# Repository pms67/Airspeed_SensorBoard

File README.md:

# Airspeed_SensorBoard
 
Differential pressure sensor breakout board with STM32 (I2C-to-SPI) interface.

Repo contains all necessary files for ordering this board, including assembly, at JLCPCB.com (https://jlcpcb.com/RHS).

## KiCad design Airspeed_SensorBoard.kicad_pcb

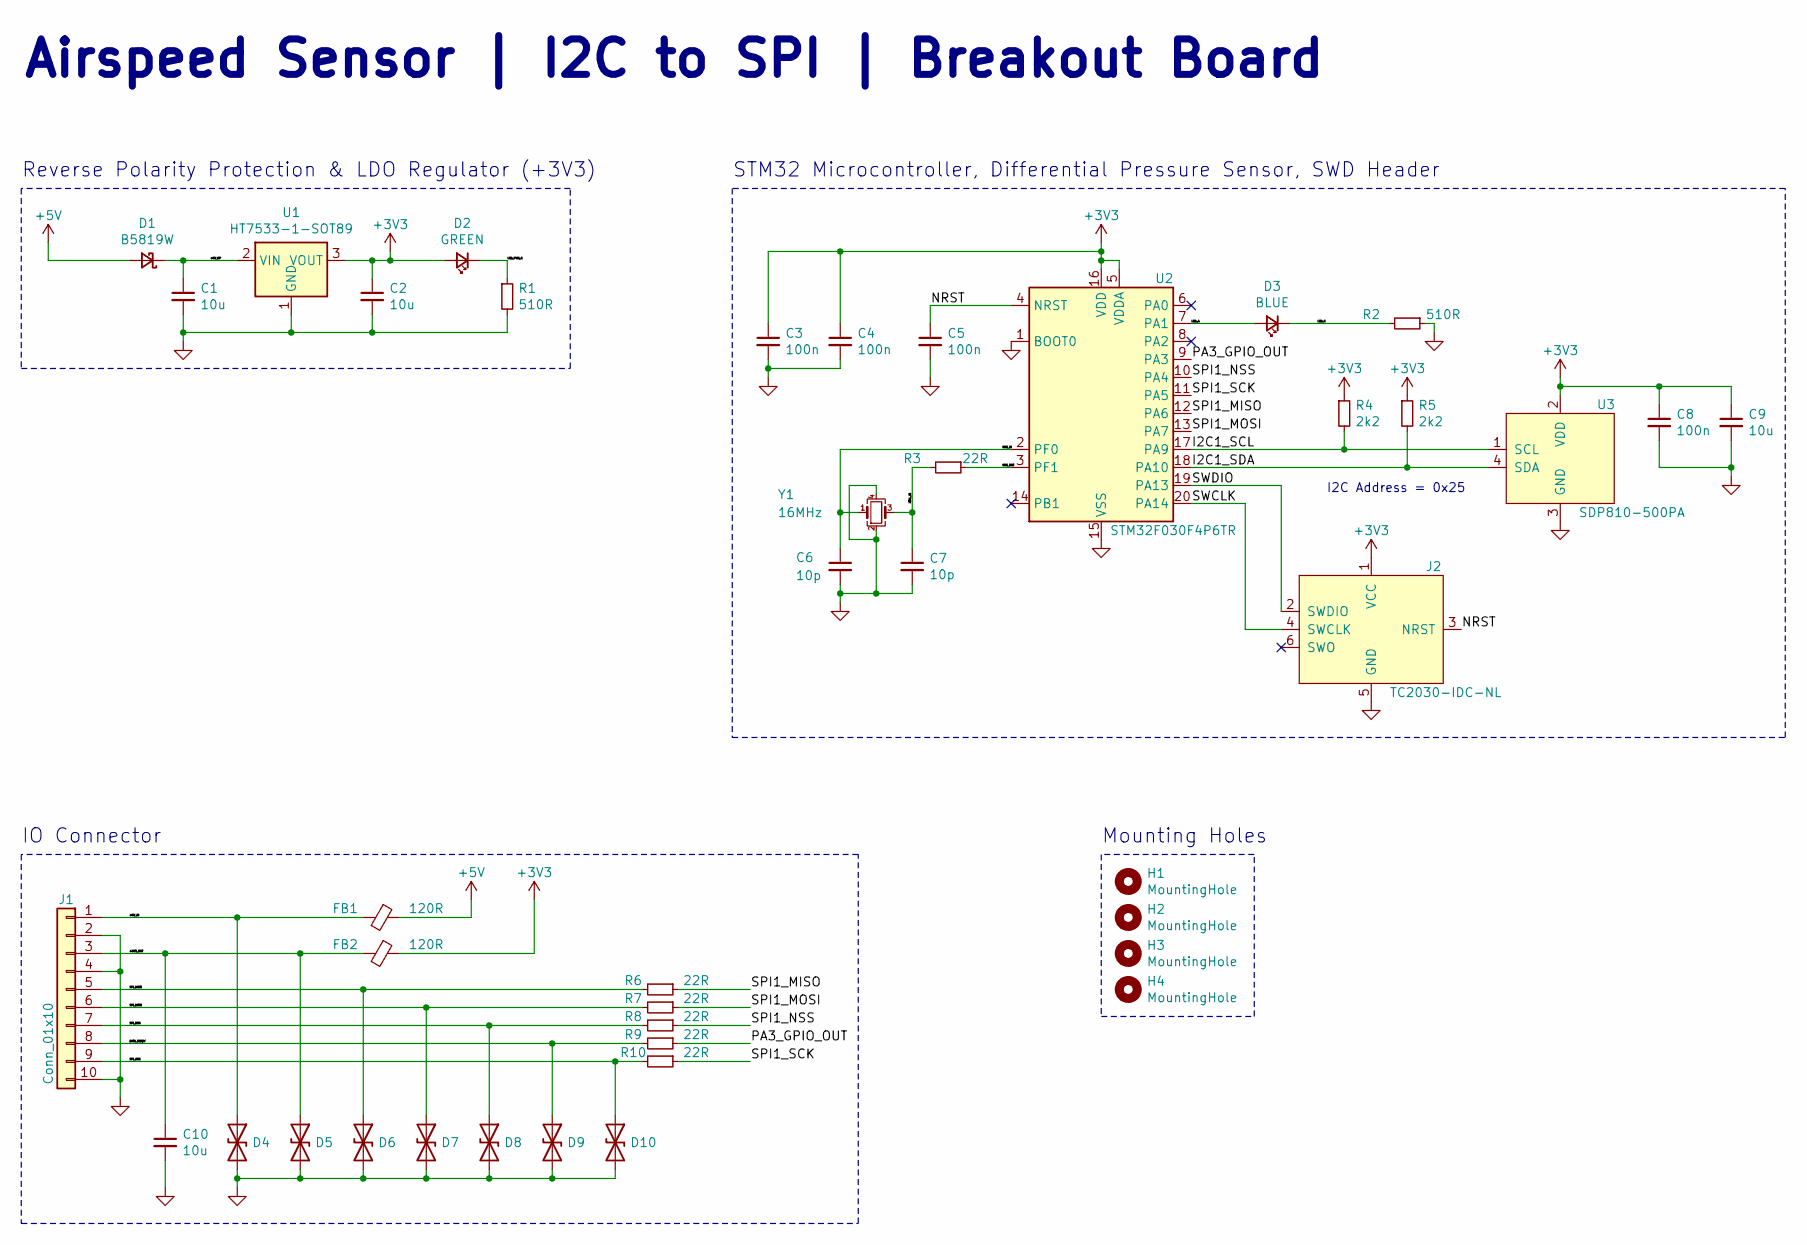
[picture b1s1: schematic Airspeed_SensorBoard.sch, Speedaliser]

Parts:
C1, C2, C9, C10: 10u; C_0805_2012Metric; LCSC Part # C15850
C3, C4, C5, C8: 100n; C_0402_1005Metric; LCSC Part # C1525
C6, C7: 10p; C_0402_1005Metric; LCSC Part # C32949
D1: B5819W; D_SOD-123; LCSC Part # C8598
D2: GREEN; LED_0603_1608Metric; LCSC Part # C72043
D3: BLUE; LED_0603_1608Metric; LCSC Part # C72041
D4, D5, D6, D7, D8, D9, D10: PESD5V0L1BA,115; D_SOD-323; LCSC Part # C85380
FB1, FB2: 120R; L_0603_1608Metric; LCSC Part # C85831
H1, H2, H3, H4: MountingHole; MountingHole_2.2mm_M2
J1: Conn_01x10; Molex_PicoBlade_53048-1010_1x10_P1.25mm_Horizontal
J2: TC2030-IDC-NL
R1, R2: 510R; R_0402_1005Metric; LCSC Part # C25123
R3, R6, R7, R8, R9, R10: 22R; R_0402_1005Metric; LCSC Part # C25092
R4, R5: 2k2; R_0402_1005Metric; LCSC Part # C25879
U1: HT7533-1-SOT89; SOT-89-3; LCSC Part # C14289
U2: STM32F030F4P6TR; TSSOP-20_4.4x6.5mm_P0.65mm; LCSC Part # C89040
U3: SDP810-500PA; LCSC Part # C153056
Y1: 16MHz; Crystal_SMD_3225-4Pin_3.2x2.5mm; LCSC Part # C13738

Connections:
+3V3: C2.1, C3.1, C4.1, C8.1, C9.1, D2.2 (A), FB2.1, J2.1 (VCC), R4.1, R5.1, U1.3 (VOUT), U2.5 (VDDA), U2.16 (VDD), U3.2 (VDD)
+5V: D1.2 (A), FB1.1
/+3V3_OUT: C10.1, D5.1 (A1), FB2.2, J1.3
/+5V_IN: D4.1 (A1), FB1.2, J1.1
/+5V_RP: C1.1, D1.1 (K), U1.2 (VIN)
/DATA_READY: D9.1 (A1), J1.8, R9.2
/HSE_IN: C6.1, U2.2 (PF0), Y1.1
/HSE_OUT: R3.1, U2.3 (PF1)
/I2C1_SCL: R4.2, U2.17 (PA9), U3.1 (SCL)
/I2C1_SDA: R5.2, U2.18 (PA10), U3.4 (SDA)
/LED_A: D3.2 (A), U2.7 (PA1)
/LED_K: D3.1 (K), R2.2
/LED_PWR_K: D2.1 (K), R1.1
/NRST: C5.1, J2.3 (NRST), U2.4 (NRST)
/PA3_GPIO_OUT: R9.1, U2.9 (PA3)
/SPI1_MISO: R6.1, U2.12 (PA6)
/SPI1_MOSI: R7.1, U2.13 (PA7)
/SPI1_NSS: R8.1, U2.10 (PA4)
/SPI1_SCK: R10.1, U2.11 (PA5)
/SPI_MISO: D6.1 (A1), J1.5, R6.2
/SPI_MOSI: D7.1 (A1), J1.6, R7.2
/SPI_NSS: D8.1 (A1), J1.7, R8.2
/SPI_SCK: D10.1 (A1), J1.9, R10.2
/SWCLK: J2.4 (SWCLK), U2.20 (PA14)
/SWDIO: J2.2 (SWDIO), U2.19 (PA13)
/XTAL_IN: C7.1, R3.2, Y1.3
GND: C1.2, C2.2, C3.2, C4.2, C5.2, C6.2, C7.2, C8.2, C9.2, C10.2, D4.2 (A2), D5.2 (A2), D6.2 (A2), D7.2 (A2), D8.2 (A2), D9.2 (A2), D10.2 (A2), J1.2, J1.4, J1.10, J2.5 (GND), R1.2, R2.1, U1.1 (GND), U2.1 (BOOT0), U2.15 (VSS), U3.3 (GND), Y1.2, Y1.4

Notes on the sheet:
I2C Address = 0x25
Reverse Polarity Protection & LDO Regulator (+3V3)
STM32 Microcontroller, Differential Pressure Sensor, SWD Header
Mounting Holes
IO Connector
Airspeed Sensor | I2C to SPI | Breakout Board

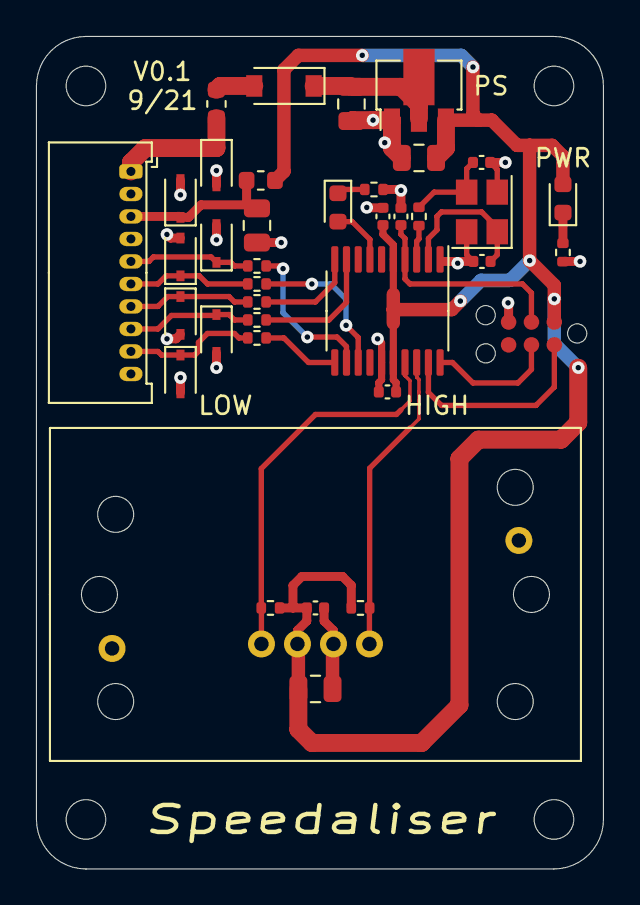
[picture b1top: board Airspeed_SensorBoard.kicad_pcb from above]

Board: 2 copper layers, 31.5 x 46.2 mm, 42 parts (0 on the bottom side), 27 nets.

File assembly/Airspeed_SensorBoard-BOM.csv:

"Designator","Quantity","Value","Cmp name","Footprint","Description","Vendor","LCSC Part #"
"C1, C2, C9, C10, ","4","10u","C_Small","Capacitor_SMD:C_0805_2012Metric","Unpolarized capacitor, small symbol","","C15850"
"C3, C4, C5, C8, ","4","100n","C_Small","Capacitor_SMD:C_0402_1005Metric","Unpolarized capacitor, small symbol","","C1525"
"C6, C7, ","2","10p","C_Small","Capacitor_SMD:C_0402_1005Metric","Unpolarized capacitor, small symbol","","C32949"
"D1, ","1","B5819W","D_Schottky_Small","Diode_SMD:D_SOD-123","Schottky diode, small symbol","","C8598"
"D2, ","1","GREEN","LED_Small","LED_SMD:LED_0603_1608Metric","Light emitting diode, small symbol","","C72043"
"D3, ","1","BLUE","LED_Small","LED_SMD:LED_0603_1608Metric","Light emitting diode, small symbol","","C72041"
"D4, D5, D6, D7, D8, D9, D10, ","7","PESD5V0L1BA,115","D_TVS","Diode_SMD:D_SOD-323","Bidirectional transient-voltage-suppression diode","","C85380"
"FB1, FB2, ","2","120R","Ferrite_Bead_Small","Inductor_SMD:L_0603_1608Metric","Ferrite bead, small symbol","","C85831"
"R1, R2, ","2","510R","R_Small","Resistor_SMD:R_0402_1005Metric","Resistor, small symbol","","C25123"
"R3, R6, R7, R8, R9, R10, ","6","22R","R_Small","Resistor_SMD:R_0402_1005Metric","Resistor, small symbol","","C25092"
"R4, R5, ","2","2k2","R_Small","Resistor_SMD:R_0402_1005Metric","Resistor, small symbol","","C25879"
"U1, ","1","HT7533-1-SOT89","HT75xx-1-SOT89","Package_TO_SOT_SMD:SOT-89-3","100mA Low Dropout Voltage Regulator, Fixed Output, SOT89","","C14289"
"U2, ","1","STM32F030F4P6TR","STM32F030F4Px","Package_SO:TSSOP-20_4.4x6.5mm_P0.65mm","ARM Cortex-M0 MCU, 16KB flash, 4KB RAM, 48MHz, 2.4-3.6V, 15 GPIO, TSSOP-20","","C89040"
"U3, ","1","SDP810-500PA","SDP810-500PA","PhilsLab-KiCad-Footprints:SDP810-500PA","","","C153056"
"Y1, ","1","16MHz","Crystal_GND24_Small","Crystal:Crystal_SMD_3225-4Pin_3.2x2.5mm","Four pin crystal, GND on pins 2 and 4, small symbol","","C13738"

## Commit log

2021-10-27 Initial commit.
